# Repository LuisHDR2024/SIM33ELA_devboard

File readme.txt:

Stack elegido JLC PCB
JLC04161H-7628

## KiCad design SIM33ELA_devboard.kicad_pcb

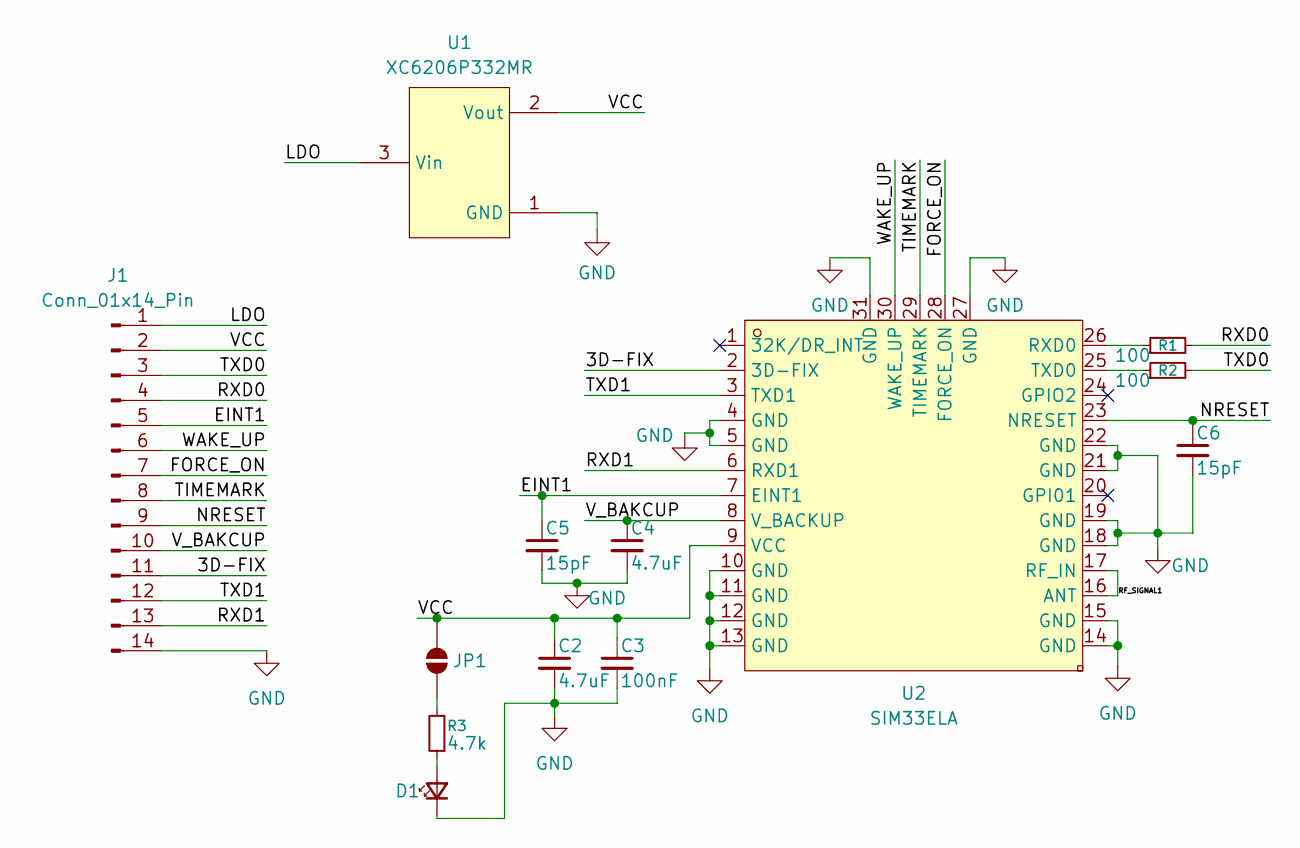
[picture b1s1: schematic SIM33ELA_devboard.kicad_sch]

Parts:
C2, C4: 4.7uF; C_0603_1608Metric
C3: 100nF; C_0603_1608Metric
C5, C6: 15pF; C_0603_1608Metric
D1: LED_Small; LED_0603_1608Metric_Pad1.05x0.95mm_HandSolder
J1: Conn_01x14_Pin; PinHeader_1x14_P2.54mm_Vertical
JP1: SolderJumper_2_Open; SolderJumper-2_P1.3mm_Open_RoundedPad1.0x1.5mm
R1, R2: 100; R_0603_1608Metric
R3: 4.7k; R_0603_1608Metric
U1: XC6206P332MR; SOT-23-3_L2.9-W1.6-P1.90-LS2.8-BR; MPN XC6206P332MR-G; LCSC Part C5446
U2: SIM33ELA; LCSC Part C6488289

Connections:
/3D-FIX: J1.11, U2.2 (3D-FIX)
/EINT1: C5.1, J1.5, U2.7 (EINT1)
/FORCE_ON: J1.7, U2.28 (FORCE_ON)
/LDO: J1.1, U1.3 (Vin)
/NRESET: C6.1, J1.9, U2.23 (NRESET)
/RF_SIGNAL1: U2.16 (ANT), U2.17 (RF_IN)
/RXD0: J1.4, R1.2
/RXD1: J1.13, U2.6 (RXD1)
/TIMEMARK: J1.8, U2.29 (TIMEMARK)
/TXD0: J1.3, R2.2
/TXD1: J1.12, U2.3 (TXD1)
/VCC: C2.1, C3.1, J1.2, JP1.2 (B), U1.2 (Vout), U2.9 (VCC)
/V_BAKCUP: C4.1, J1.10, U2.8 (V_BACKUP)
/WAKE_UP: J1.6, U2.30 (WAKE_UP)
GND: C2.2, C3.2, C4.2, C5.2, C6.2, D1.1 (K), J1.14, U1.1 (GND), U2.4 (GND), U2.5 (GND), U2.10 (GND), U2.11 (GND), U2.12 (GND), U2.13 (GND), U2.14 (GND), U2.15 (GND), U2.18 (GND), U2.19 (GND), U2.21 (GND), U2.22 (GND), U2.27 (GND), U2.31 (GND)
unnamed: D1.2 (A), R3.1
unnamed: JP1.1 (A), R3.2
unnamed: R1.1, U2.26 (RXD0)
unnamed: R2.1, U2.25 (TXD0)

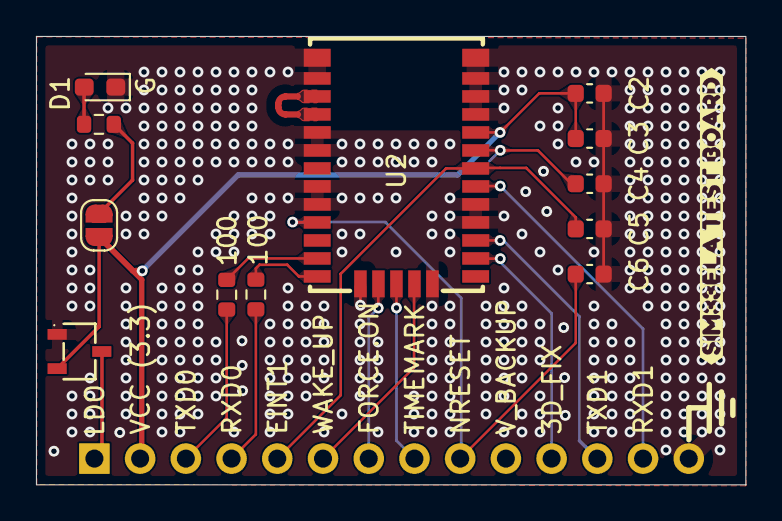
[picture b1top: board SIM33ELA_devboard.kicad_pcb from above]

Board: 4 copper layers, 39.4 x 24.9 mm, 14 parts (1 on the bottom side), 19 nets.

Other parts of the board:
kibuzzard-6A1C62F4: G***; kibuzzard-6A1C62F4

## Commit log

2026-02-12 version final
2026-03-25 RF modificado, agregado led de POWER
2026-03-26 por si acaso
2026-03-26 agregado readme
2026-03-27 cambio de stack JLCPCB, 2 versiones para microstrip
2026-03-30 cambios finales
2026-05-16 diseño final
